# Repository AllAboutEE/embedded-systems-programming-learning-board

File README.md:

# embedded-systems-programming-learning-board
A circuit board with examples in several microcontroller architectures to help people learn microcontrollers programming.

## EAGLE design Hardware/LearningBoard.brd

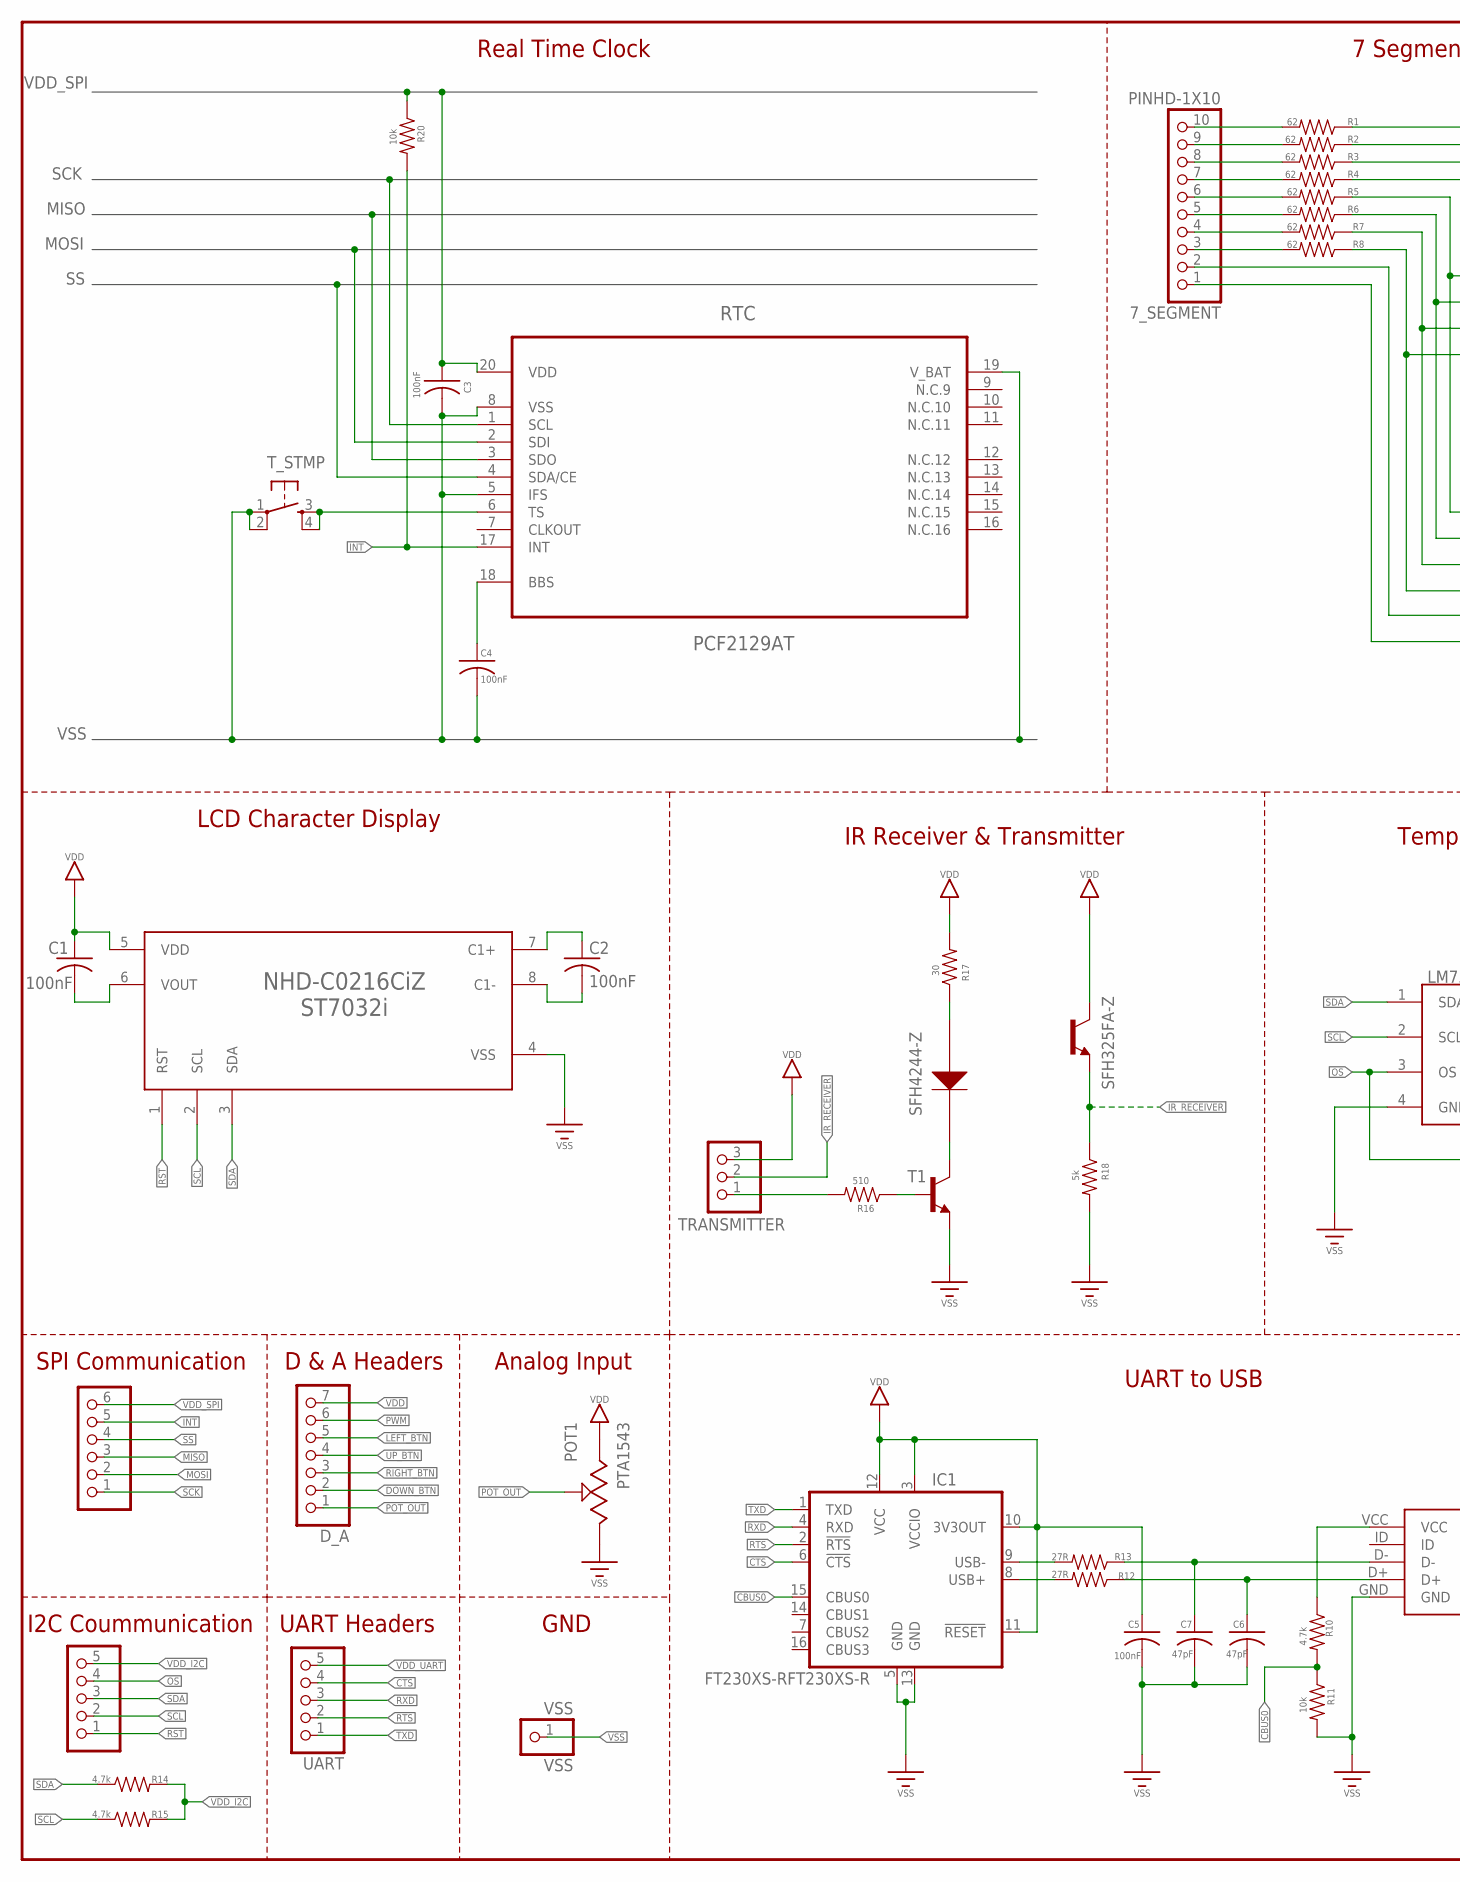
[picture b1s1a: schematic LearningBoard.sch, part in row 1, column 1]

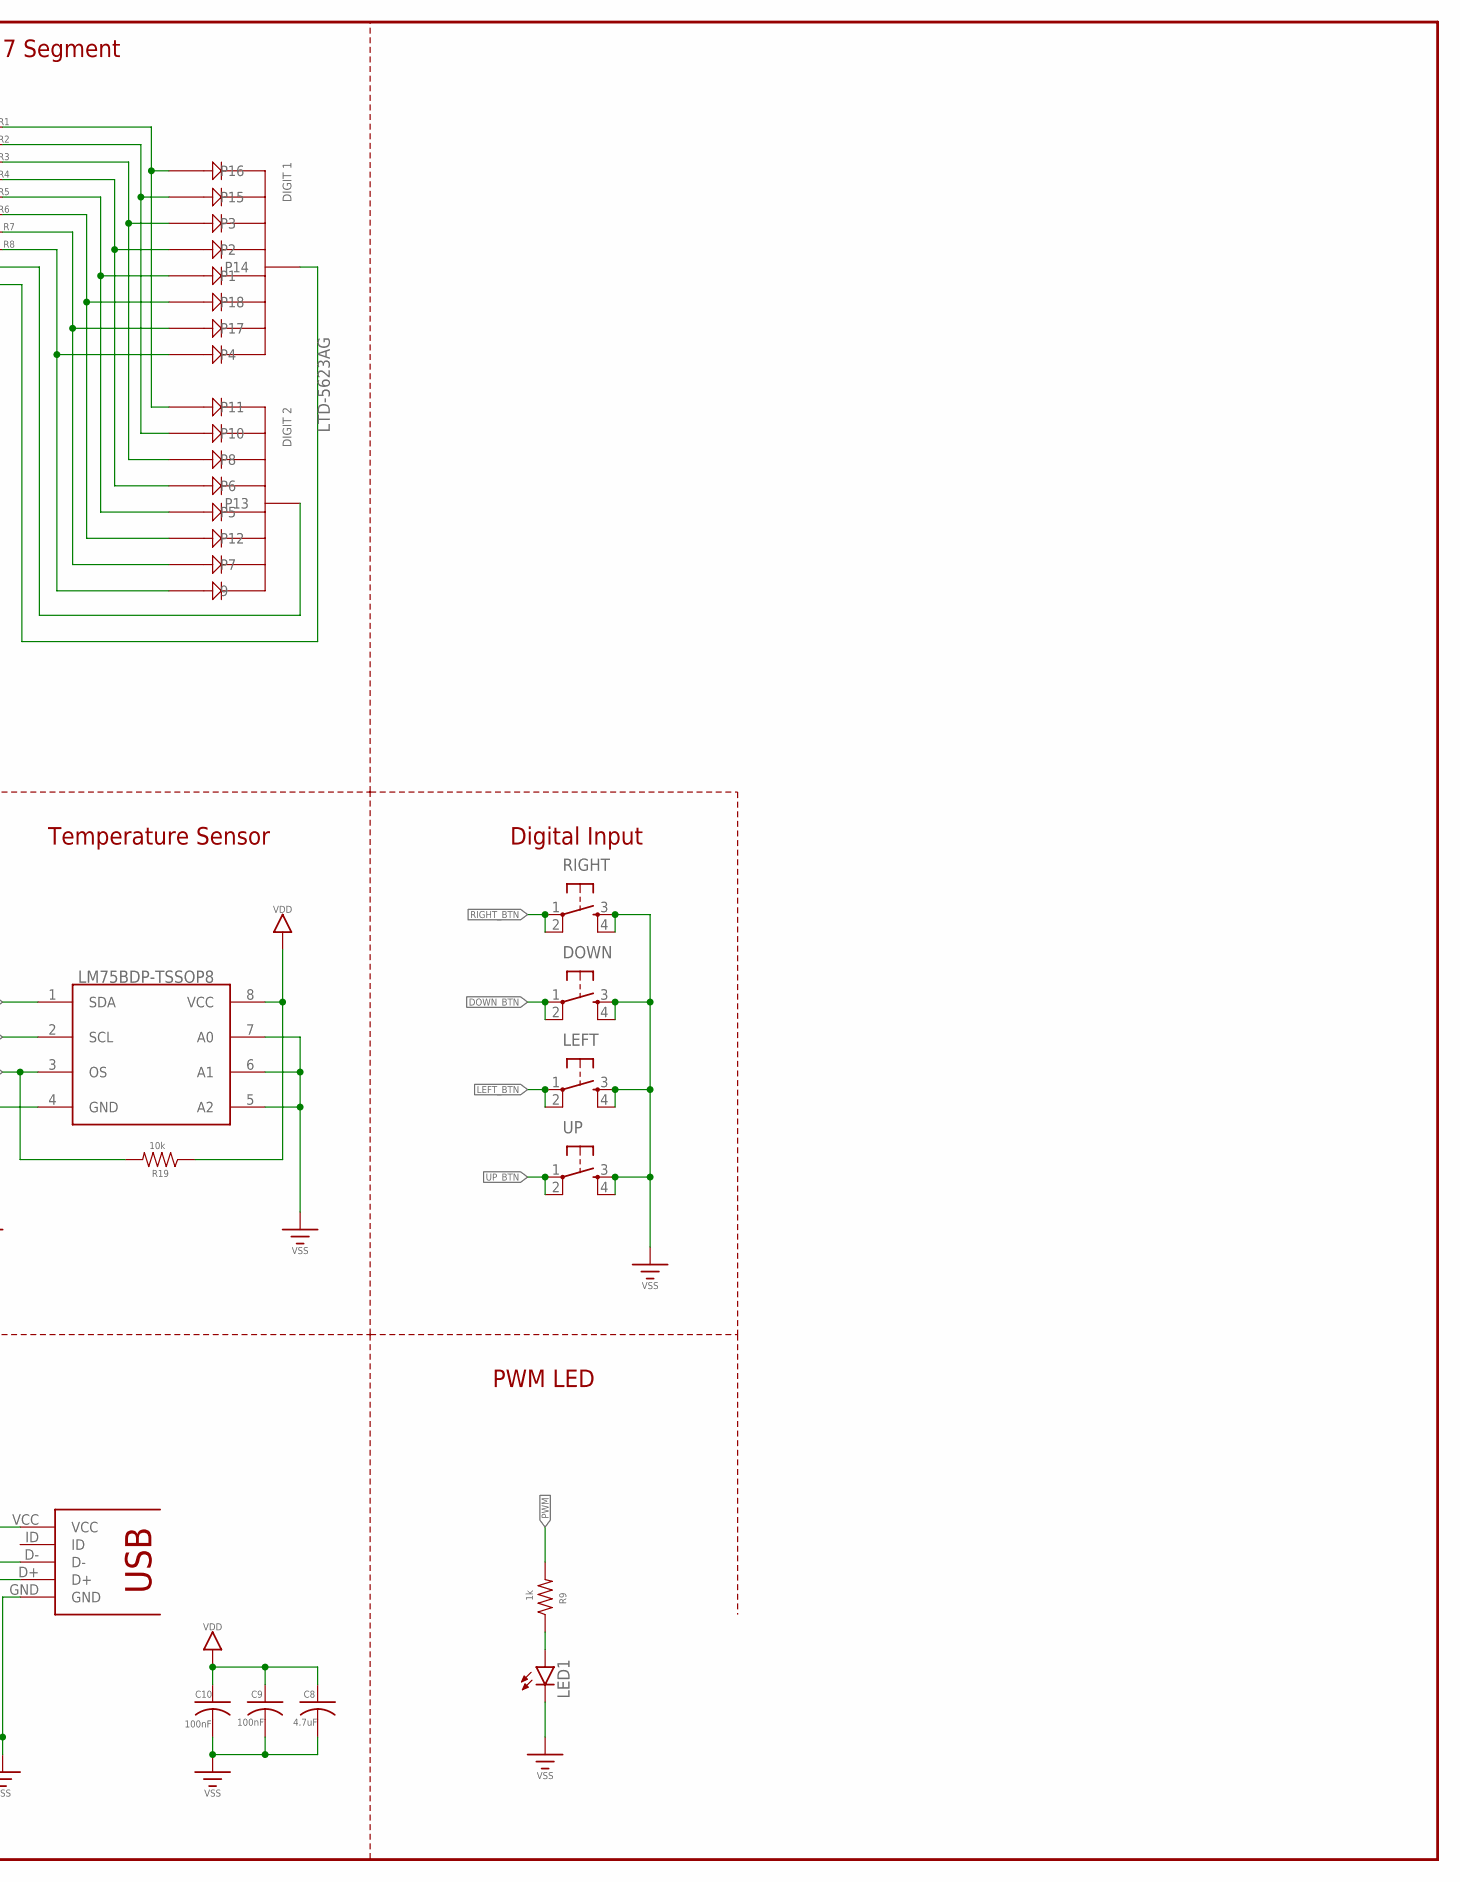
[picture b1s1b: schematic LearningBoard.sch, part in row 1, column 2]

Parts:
7_SEGMENT: PINHD-1X10; 1X10-BIG
C1, C2, C3, C4, C5, C9, C10: 100nF; C0805
C6, C7: 47pF; C0805
C8: 4.7uF; C0805
DOWN: TAC_SWITCHPTH; TACTILE-PTH
D_A: PINHD-1X7; 1X07
I2C: PINHD-1X5; 1X05
IC1: FT230XS-RFT230XS-R; FT230XS-R
LED1: LED5MM
LEFT: TAC_SWITCHPTH; TACTILE-PTH
POT1: PTA1543
R1, R2, R3, R4, R5, R6, R7, R8: 62; 0805
R9: 1k; 0805
R10, R14, R15: 4.7k; 0805
R11, R19, R20: 10k; 0805
R12, R13: 27R; 0805
R16: 510; 0805
R17: 30; 0805
R18: 5k; 0805
RECEIVER_: SFH325FA-Z
RIGHT: TAC_SWITCHPTH; TACTILE-PTH
SPI: PINHD-1X6; 1X06
T1: MMBT3904LT1-NPN-SOT23-BEC; SOT23-BEC
TRANSMITTER: PINHD-1X3; 1X03
TRANSMITTER_: SFH4244-Z
T_STMP: TAC_SWITCHPTH; TACTILE-PTH
U$1: PCF2129AT
U$2: NHD-C0216CIZ-FN-FBW-3V
U$3: LTD-5623AG
U$10: 10118192-0001LF
U$11: LM75BDP-TSSOP8; TSSOP8
UART: PINHD-1X5; 1X05
UP: TAC_SWITCHPTH; TACTILE-PTH
VSS: VSS; 1X01

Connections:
CBUS0: IC1.15 (CBUS0), R10.2, R11.1
CTS: IC1.6 (!CTS), UART.4
DIN: R16.2, TRANSMITTER.1
DOWN_BTN: DOWN.1, DOWN.2, D_A.2
INT: R20.2, SPI.5, U$1.17 (INT)
IR_RECEIVER: R18.1, RECEIVER_.E, TRANSMITTER.2
LEFT_BTN: D_A.5, LEFT.1, LEFT.2
MISO: SPI.3, U$1.3 (SDO)
MOSI: SPI.2, U$1.2 (SDI)
unnamed: C1.2, U$2.6 (VOUT)
unnamed: C2.1, U$2.7 (C1+)
unnamed: C2.2, U$2.8 (C1-)
unnamed: LED1.A, R9.1
unnamed: R1.1, U$3.P11, U$3.P16
unnamed: R2.1, U$3.P10, U$3.P15
unnamed: R4.1, U$3.P2, U$3.P6
unnamed: R3.1, U$3.P3, U$3.P8
unnamed: R5.1, U$3.P1, U$3.P5
unnamed: R6.1, U$3.P12, U$3.P18
unnamed: R7.1, U$3.P7, U$3.P17
unnamed: R8.1, U$3.P4, U$3.P9 (9)
unnamed: 7_SEGMENT.10, R1.2
unnamed: 7_SEGMENT.9, R2.2
unnamed: 7_SEGMENT.8, R3.2
unnamed: 7_SEGMENT.7, R4.2
unnamed: 7_SEGMENT.6, R5.2
unnamed: 7_SEGMENT.5, R6.2
unnamed: 7_SEGMENT.4, R7.2
unnamed: 7_SEGMENT.3, R8.2
unnamed: 7_SEGMENT.2, U$3.P13
unnamed: 7_SEGMENT.1, U$3.P14
unnamed: T1.C, TRANSMITTER_.C
unnamed: R17.1, TRANSMITTER_.A
unnamed: R16.1, T1.B
unnamed: T_STMP.3, T_STMP.4, U$1.6 (TS)
unnamed: C4.1, U$1.18 (BBS)
unnamed: IC1.9 (USB-), R13.2
unnamed: C7.1, R13.1, U$10.D-
unnamed: C6.1, R12.1, U$10.D+
unnamed: IC1.8 (USB+), R12.2
unnamed: R10.1, U$10.VCC
OS: I2C.4, R19.2, U$11.3 (OS)
POT_OUT: D_A.1, POT1.2
PWM: D_A.6, R9.2
RIGHT_BTN: D_A.3, RIGHT.1, RIGHT.2
RST: I2C.1, U$2.1 (RST)
RTS: IC1.2 (!RTS), UART.2
RXD: IC1.4 (RXD), UART.3
SCK: SPI.1, U$1.1 (SCL)
SCL: I2C.2, R15.1, U$2.2 (SCL), U$11.2 (SCL)
SDA: I2C.3, R14.1, U$2.3 (SDA), U$11.1 (SDA)
SS: SPI.4, U$1.4 (SDA/CE)
TXD: IC1.1 (TXD), UART.1
UP_BTN: D_A.4, UP.1, UP.2
VDD: D_A.7, POT1.3
VDD_I2C: C1.1, I2C.5, R14.2, R15.2, R19.1, U$2.5 (VDD), U$11.8 (VCC)
VDD_IR: R17.2, RECEIVER_.C, TRANSMITTER.3
VDD_SPI: C3.1, R20.1, SPI.6, U$1.20 (VDD)
VDD_UART: C5.1, C8.1, C9.1, C10.1, IC1.3 (VCCIO), IC1.10 (3V3OUT), IC1.11 (!RESET), IC1.12 (VCC), UART.5
VSS: C3.2, C4.2, C5.2, C6.2, C7.2, C8.2, C9.2, C10.2, DOWN.3, DOWN.4, IC1.5 (GND), IC1.13 (GND), LED1.K (C), LEFT.3, LEFT.4, POT1.1, R11.2, R18.2, RIGHT.3, RIGHT.4, T1.E, T_STMP.1, T_STMP.2, U$1.5 (IFS), U$1.8 (VSS), U$1.19 (V_BAT), U$2.4 (VSS), U$10.GND, U$11.4 (GND), U$11.5 (A2), U$11.6 (A1), U$11.7 (A0), UP.3, UP.4, VSS.1

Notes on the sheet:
LCD Character Display
7 Segment
SPI Communication
Analog Input
D & A Headers
Digital Input
IR Receiver & Transmitter
Temperature Sensor
Real Time Clock
UART to USB
UART Headers
I2C Coummunication
PWM LED
GND

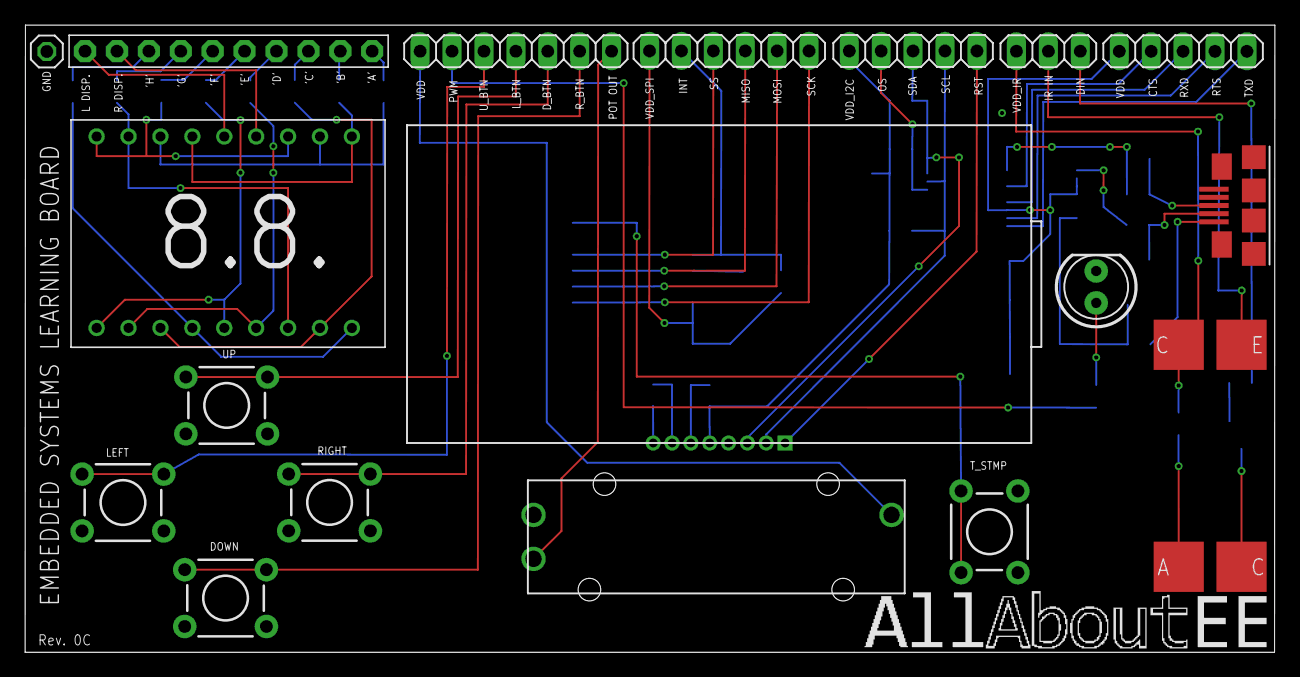
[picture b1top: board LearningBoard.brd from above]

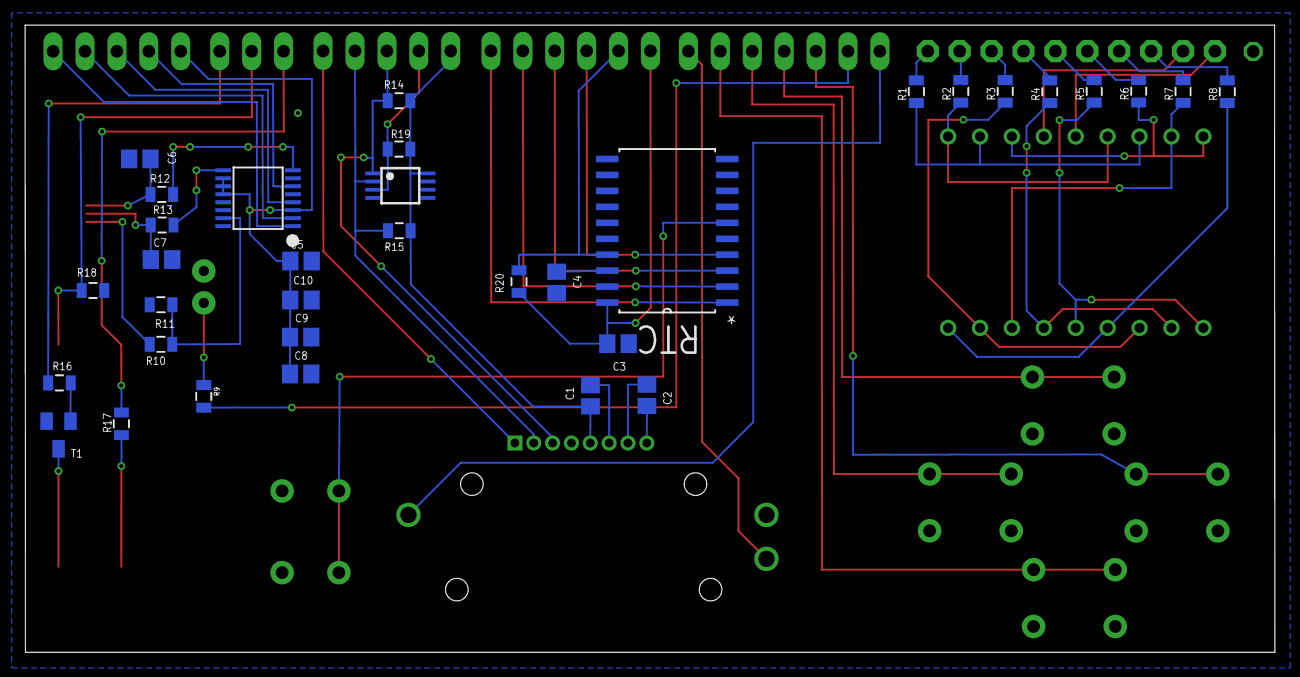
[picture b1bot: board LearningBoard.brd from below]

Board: 2 copper layers, 99.5 x 49.9 mm, 53 parts (34 on the bottom side), 60 nets.

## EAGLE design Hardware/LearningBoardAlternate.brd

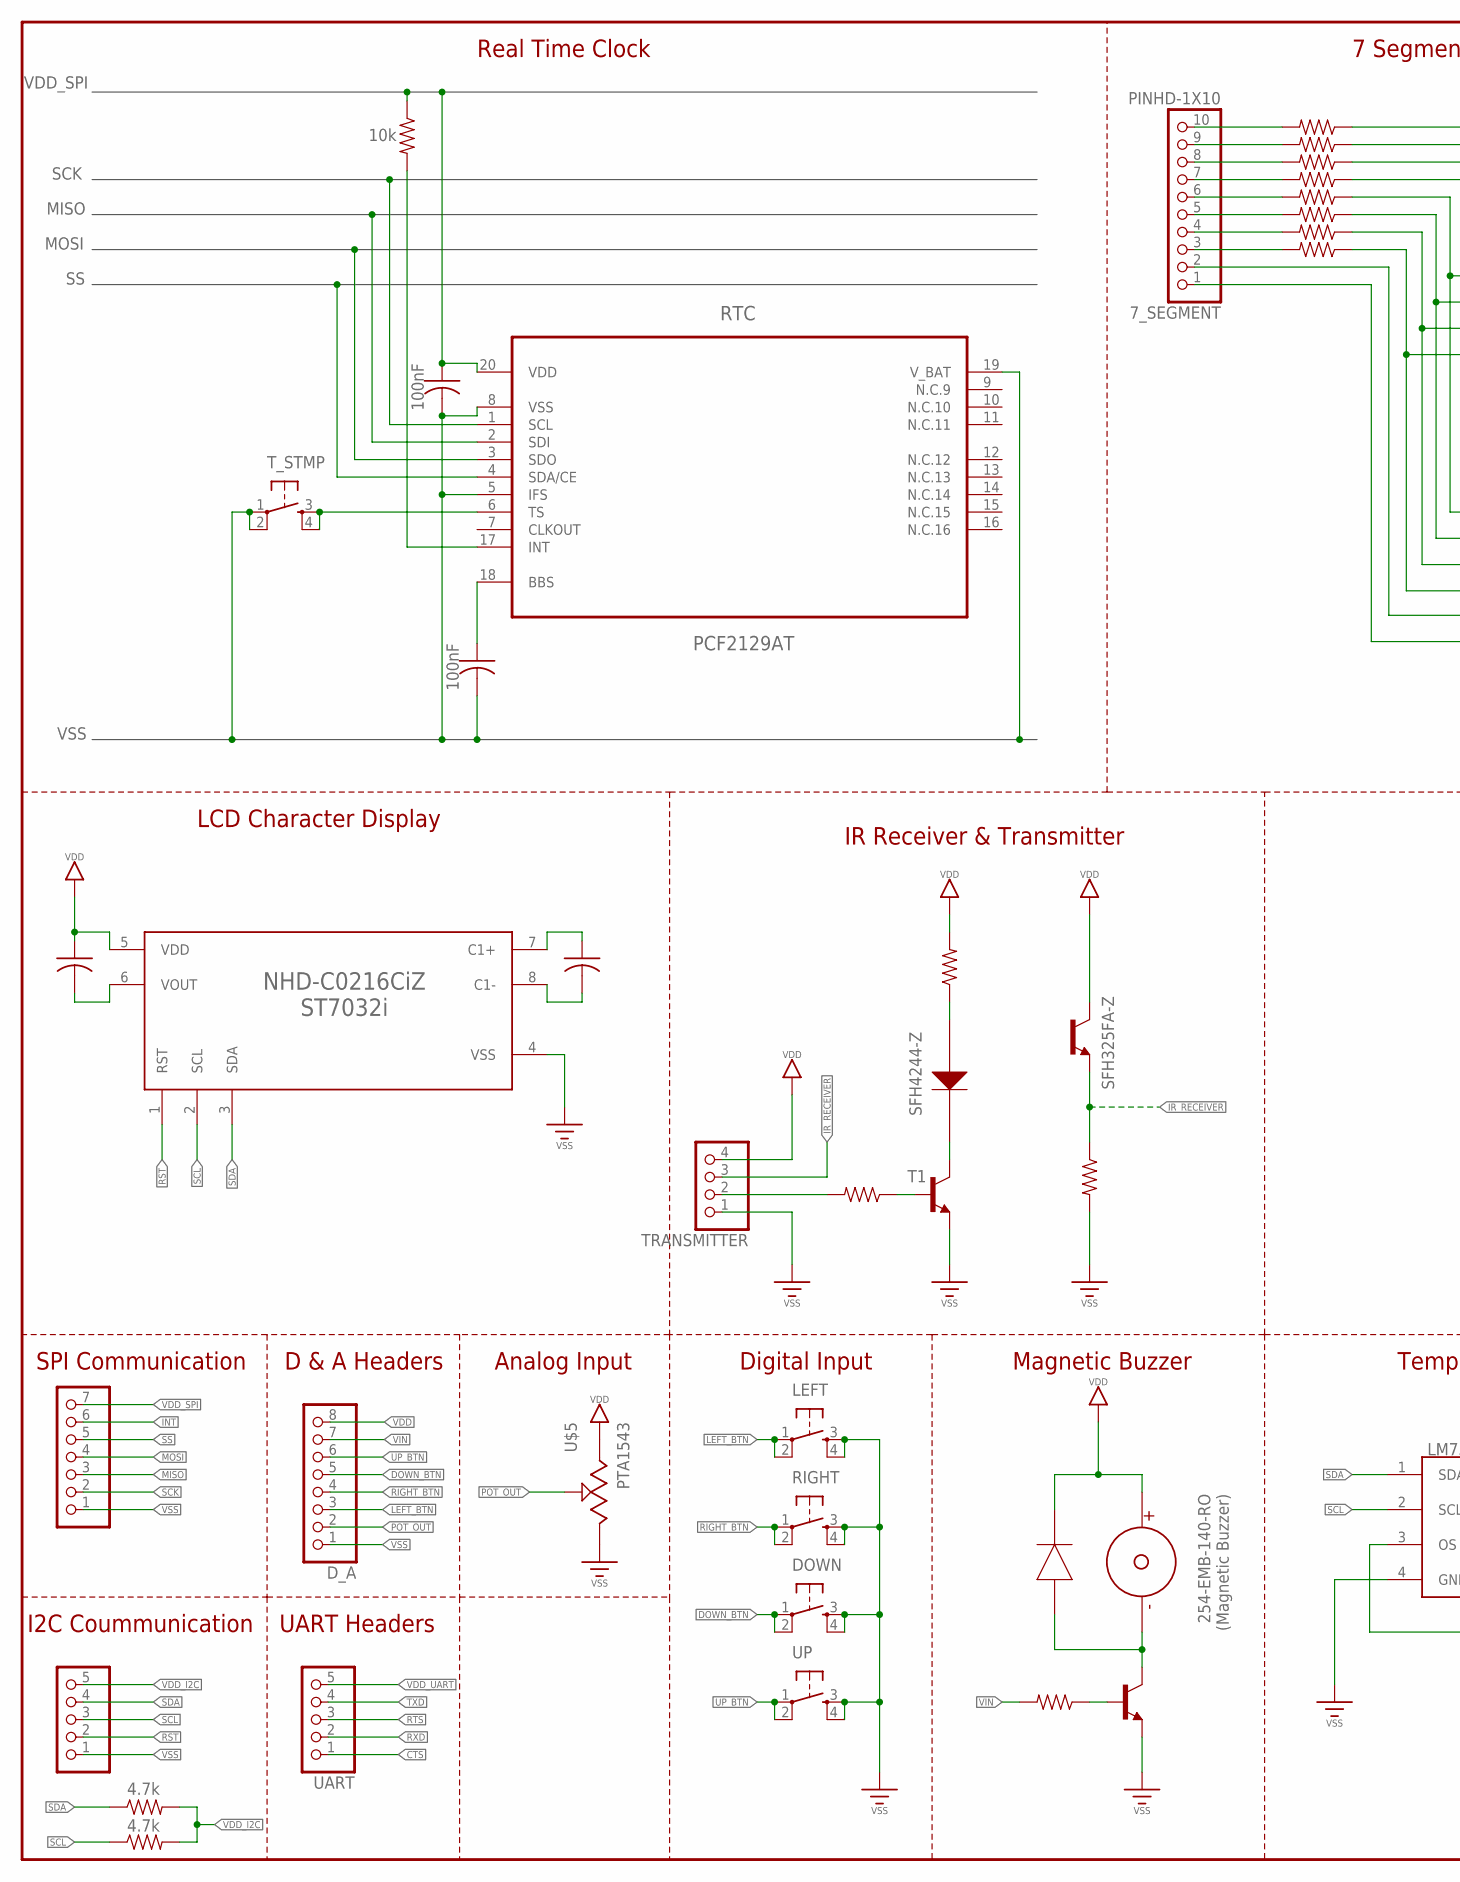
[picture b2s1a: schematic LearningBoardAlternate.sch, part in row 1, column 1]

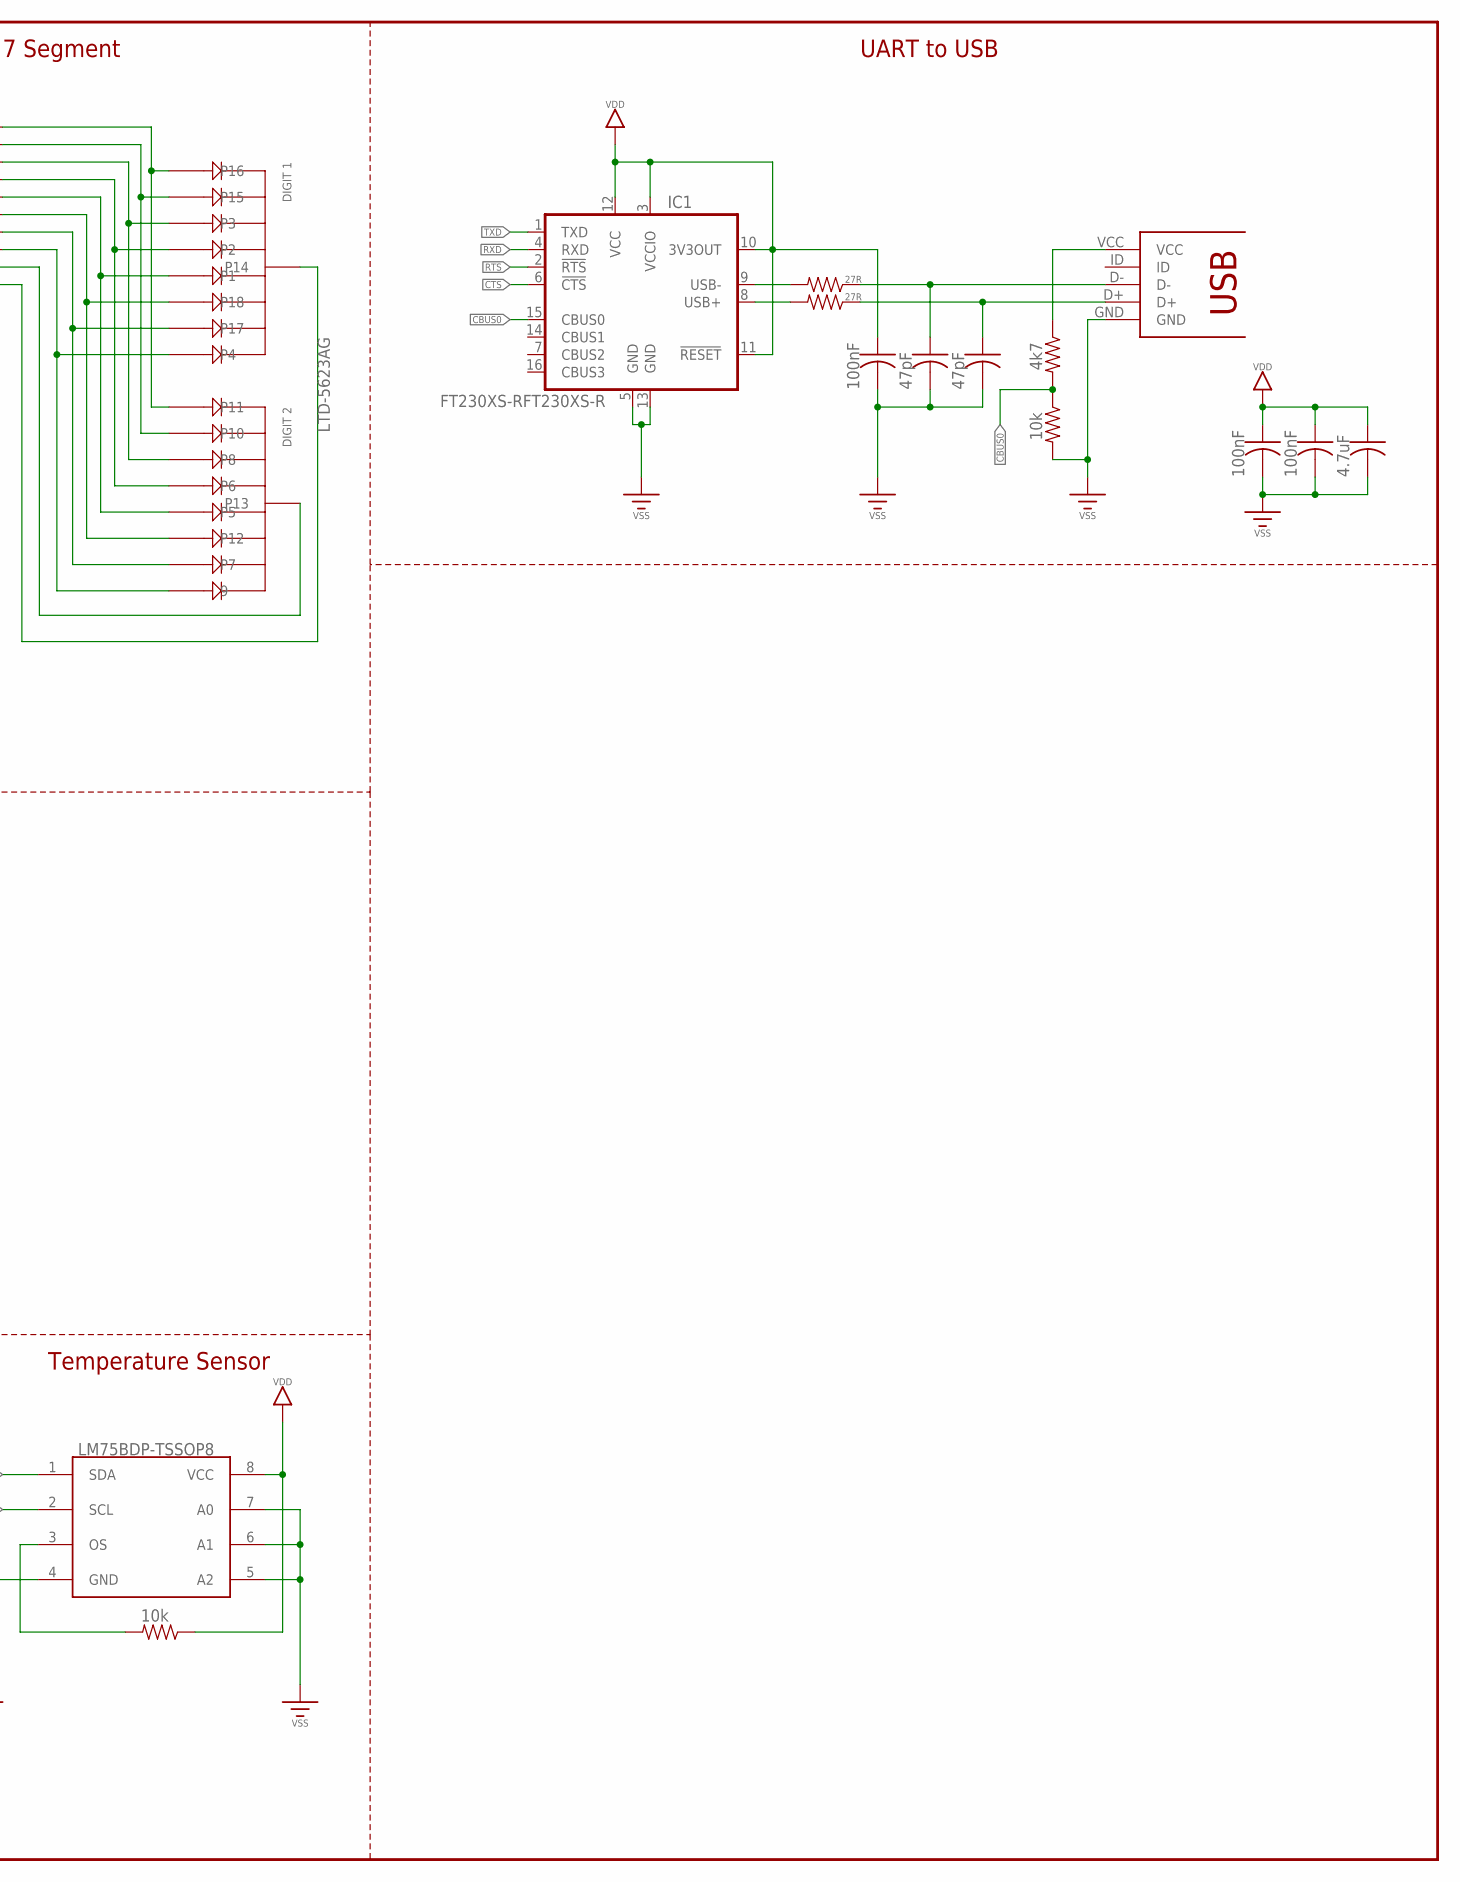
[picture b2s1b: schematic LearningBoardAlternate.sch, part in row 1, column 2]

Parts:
7_SEGMENT: PINHD-1X10; 1X10-BIG
C1, C2, C3, C4, C5, C9, C10: 100nF; C0805
C6, C7: 47pF; C0805
C8: 4.7uF; C0805
DOWN: TAC_SWITCHPTH; TACTILE-PTH
D_A: PINHD-1X8; 1X08
I2C: PINHD-1X5; 1X05
IC1: FT230XS-RFT230XS-R; FT230XS-R
LEFT: TAC_SWITCHPTH; TACTILE-PTH
RECEIVER_: SFH325FA-Z
RIGHT: TAC_SWITCHPTH; TACTILE-PTH
RPU1, RPU2, RPU3, RPU7, RPU8, RPU9, RPU10, RPU11, RPU16, RPU17: 4.7k; 0805
RPU4, RPU5, RPU12, RPU13, RPU14, RPU15, RPU20: 10k; 0805
RPU6, RPU18: 27R; 0805
RPU19: 4k7; 0805
SPI: PINHD-1X7; 1X07
T1, T2: MMBT3904LT1-NPN-SOT23-BEC; SOT23-BEC
TRANSMITTER: PINHD-1X4; 1X04
TRANSMITTER_: SFH4244-Z
T_STMP: TAC_SWITCHPTH; TACTILE-PTH
U$1: PCF2129AT
U$2: NHD-C0216CIZ-FN-FBW-3V
U$3: LTD-5623AG
U$5: PTA1543
U$8: 254-EMB-140-RO
U$9: 1N4148X-TP; SOD523
U$10: 10118192-0001LF
U$11: LM75BDP-TSSOP8; TSSOP8
UART: PINHD-1X5; 1X05
UP: TAC_SWITCHPTH; TACTILE-PTH

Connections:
CBUS0: IC1.15 (CBUS0), RPU19.2, RPU20.1
CTS: IC1.6 (!CTS), UART.1
DIN: RPU13.2, TRANSMITTER.2
DOWN_BTN: DOWN.1, DOWN.2, D_A.5
INT: RPU4.2, SPI.6, U$1.17 (INT)
IR_RECEIVER: RECEIVER_.E, RPU14.1, TRANSMITTER.3
LEFT_BTN: D_A.3, LEFT.1, LEFT.2
MISO: SPI.3, U$1.2 (SDI)
MOSI: SPI.4, U$1.3 (SDO)
unnamed: C1.2, U$2.6 (VOUT)
unnamed: C2.1, U$2.7 (C1+)
unnamed: C2.2, U$2.8 (C1-)
unnamed: T2.C, U$8.NEGATIVE, U$9.A
unnamed: RPU1.1, U$3.P11, U$3.P16
unnamed: RPU2.1, U$3.P10, U$3.P15
unnamed: RPU7.1, U$3.P2, U$3.P6
unnamed: RPU3.1, U$3.P3, U$3.P8
unnamed: RPU8.1, U$3.P1, U$3.P5
unnamed: RPU9.1, U$3.P12, U$3.P18
unnamed: RPU10.1, U$3.P7, U$3.P17
unnamed: RPU11.1, U$3.P4, U$3.P9 (9)
unnamed: 7_SEGMENT.10, RPU1.2
unnamed: 7_SEGMENT.9, RPU2.2
unnamed: 7_SEGMENT.8, RPU3.2
unnamed: 7_SEGMENT.7, RPU7.2
unnamed: 7_SEGMENT.6, RPU8.2
unnamed: 7_SEGMENT.5, RPU9.2
unnamed: 7_SEGMENT.4, RPU10.2
unnamed: 7_SEGMENT.3, RPU11.2
unnamed: 7_SEGMENT.2, U$3.P13
unnamed: 7_SEGMENT.1, U$3.P14
unnamed: T1.C, TRANSMITTER_.C
unnamed: RPU12.1, TRANSMITTER_.A
unnamed: RPU13.1, T1.B
unnamed: T_STMP.3, T_STMP.4, U$1.6 (TS)
unnamed: RPU15.1, T2.B
unnamed: C4.1, U$1.18 (BBS)
unnamed: RPU5.2, U$11.3 (OS)
unnamed: IC1.9 (USB-), RPU6.2
unnamed: C7.1, RPU6.1, U$10.D-
unnamed: C6.1, RPU18.1, U$10.D+
unnamed: IC1.8 (USB+), RPU18.2
unnamed: RPU19.1, U$10.VCC
POT_OUT: D_A.2, U$5.2
RIGHT_BTN: D_A.4, RIGHT.1, RIGHT.2
RST: I2C.2, U$2.1 (RST)
RTS: IC1.2 (!RTS), UART.3
RXD: IC1.4 (RXD), UART.2
SCK: SPI.2, U$1.1 (SCL)
SCL: I2C.3, RPU17.1, U$2.2 (SCL), U$11.2 (SCL)
SDA: I2C.4, RPU16.1, U$2.3 (SDA), U$11.1 (SDA)
SS: SPI.5, U$1.4 (SDA/CE)
TXD: IC1.1 (TXD), UART.4
UP_BTN: D_A.6, UP.1, UP.2
VDD: D_A.8, U$5.3, U$8.POSITIVE, U$9.C
VDD_I2C: C1.1, I2C.5, RPU5.1, RPU16.2, RPU17.2, U$2.5 (VDD), U$11.8 (VCC)
VDD_IR: RECEIVER_.C, RPU12.2, TRANSMITTER.4
VDD_SPI: C3.1, RPU4.1, SPI.7, U$1.20 (VDD)
VDD_UART: C5.1, C8.1, C9.1, C10.1, IC1.3 (VCCIO), IC1.10 (3V3OUT), IC1.11 (!RESET), IC1.12 (VCC), UART.5
VIN: D_A.7, RPU15.2
VSS: C3.2, C4.2, C5.2, C6.2, C7.2, C8.2, C9.2, C10.2, DOWN.3, DOWN.4, D_A.1, I2C.1, IC1.5 (GND), IC1.13 (GND), LEFT.3, LEFT.4, RIGHT.3, RIGHT.4, RPU14.2, RPU20.2, SPI.1, T1.E, T2.E, TRANSMITTER.1, T_STMP.1, T_STMP.2, U$1.5 (IFS), U$1.8 (VSS), U$1.19 (V_BAT), U$2.4 (VSS), U$5.1, U$10.GND, U$11.4 (GND), U$11.5 (A2), U$11.6 (A1), U$11.7 (A0), UP.3, UP.4

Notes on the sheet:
LCD Character Display
7 Segment
SPI Communication
Analog Input
D & A Headers
Digital Input
IR Receiver & Transmitter
Magnetic Buzzer
Temperature Sensor
Real Time Clock
UART to USB
UART Headers
I2C Coummunication

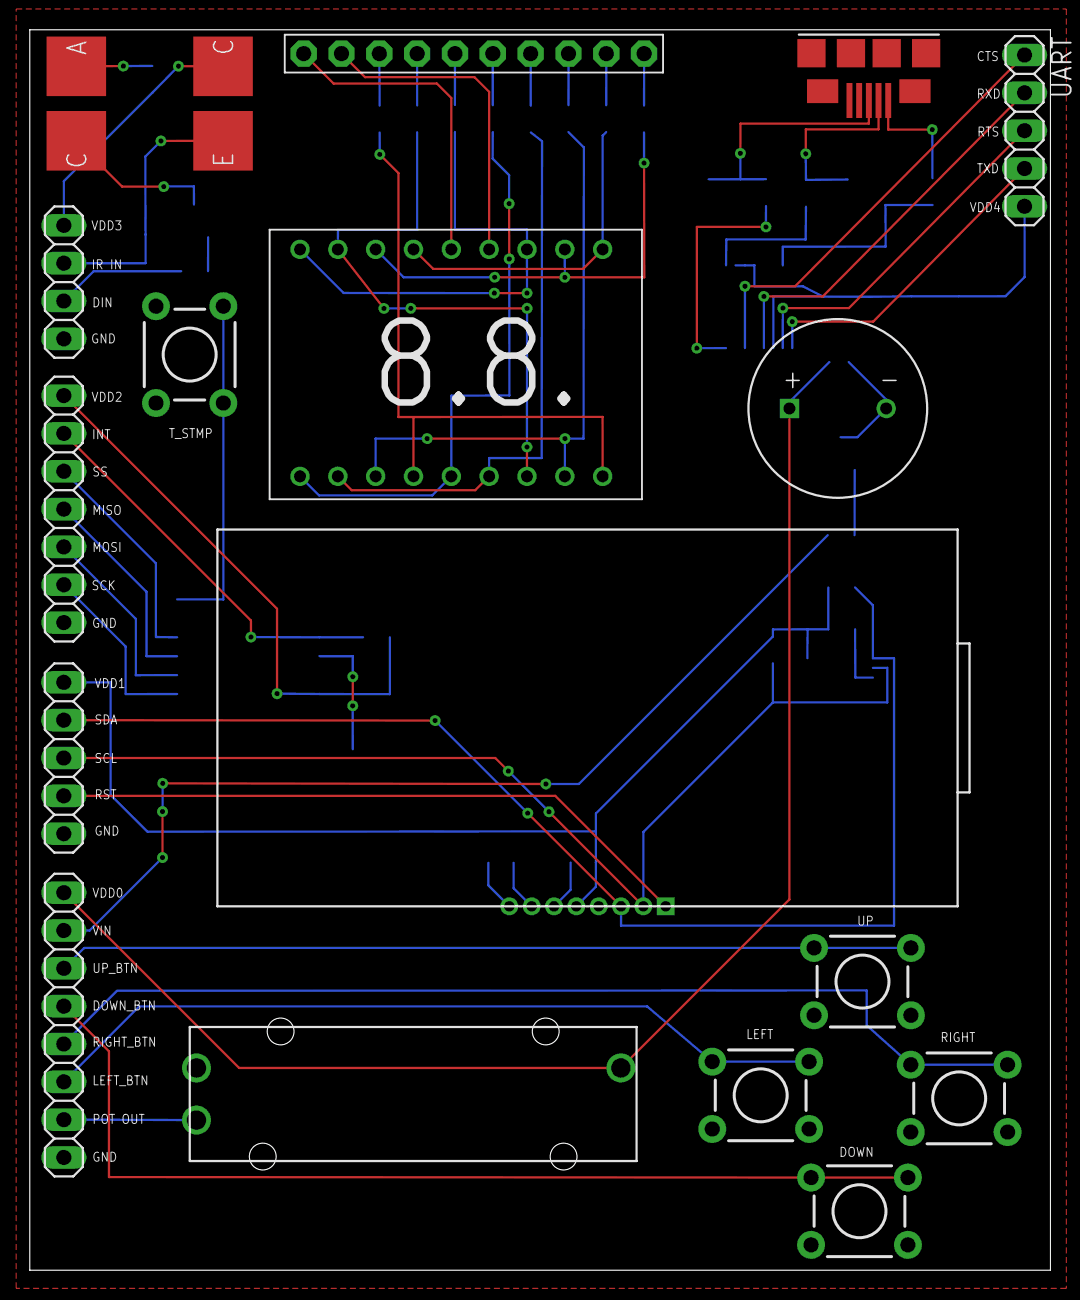
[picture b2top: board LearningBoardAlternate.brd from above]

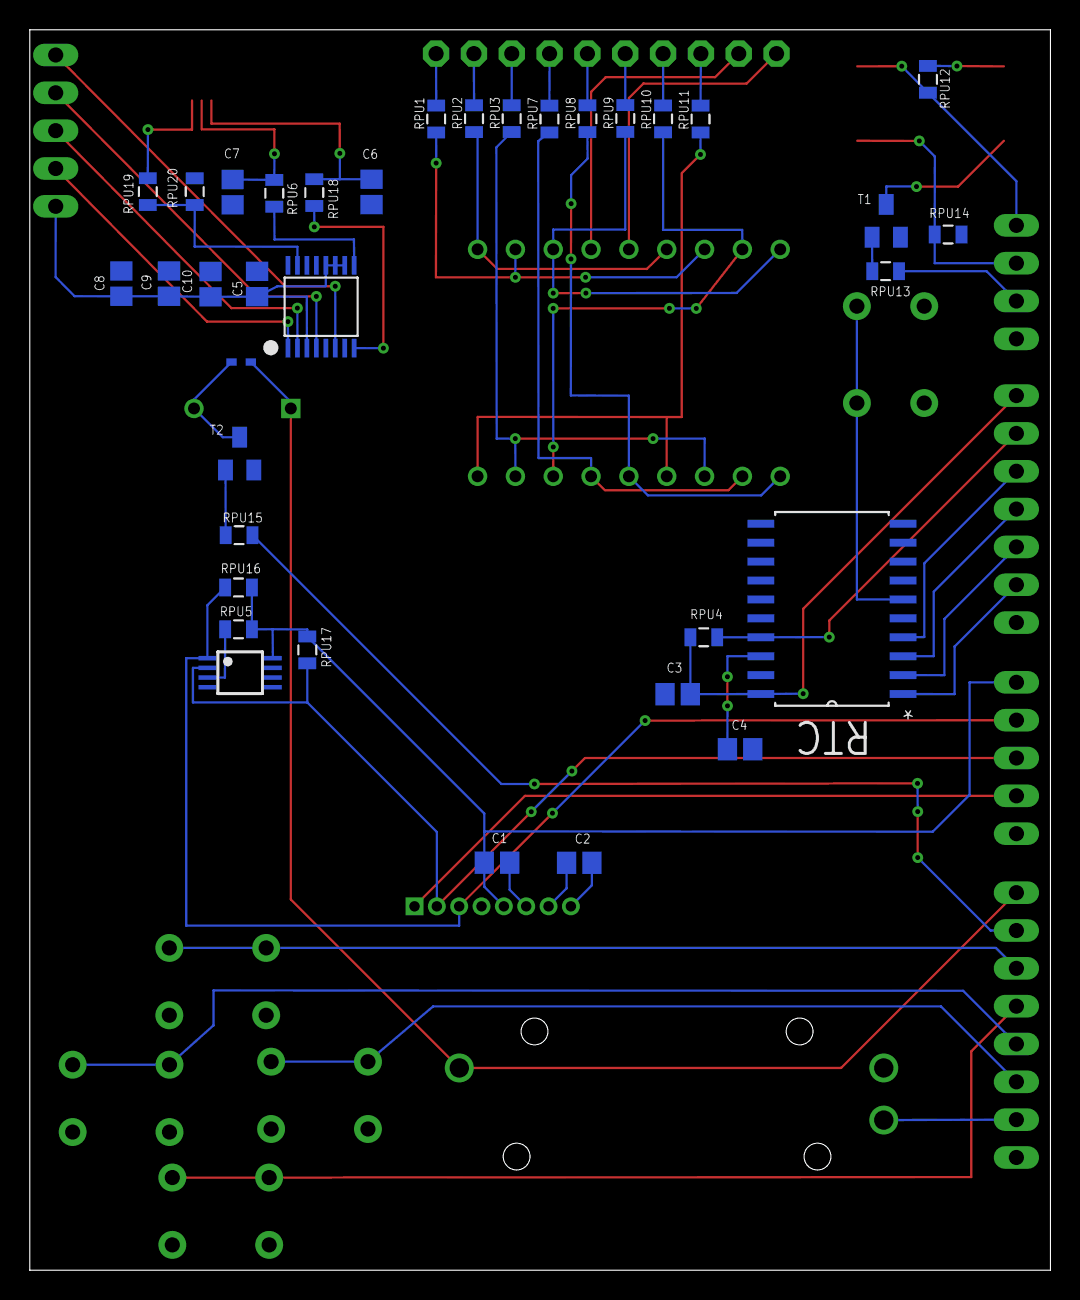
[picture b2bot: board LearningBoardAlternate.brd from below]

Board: 2 copper layers, 68.5 x 83.3 mm, 54 parts (36 on the bottom side), 61 nets.

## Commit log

2015-08-02 Crated PCB layout 0.0.0
2015-08-02 Created an Alternate PCB design to reduce cost
2015-08-04 Finished the alternate PCB design
2015-08-05 Updated parts on board and part labels
2015-08-08 Completed first PCB design ready for OSHPark. REmoved alternate PCB design file created only 1.
2015-08-14 - Added some resistor values - Changed resistor names (removed UP string).
2016-04-18 New slim design.

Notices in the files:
parts and their libraries:
SparkFun-Passives: Licensing: Creative Commons ShareAlike 4.0 International - https://creativecommons.org/licenses/by-sa/4.0
